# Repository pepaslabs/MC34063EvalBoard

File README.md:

# MC34063InvertingEvalBoard
An evaluation board for use with the MC34063 switcher in inverting configuration.

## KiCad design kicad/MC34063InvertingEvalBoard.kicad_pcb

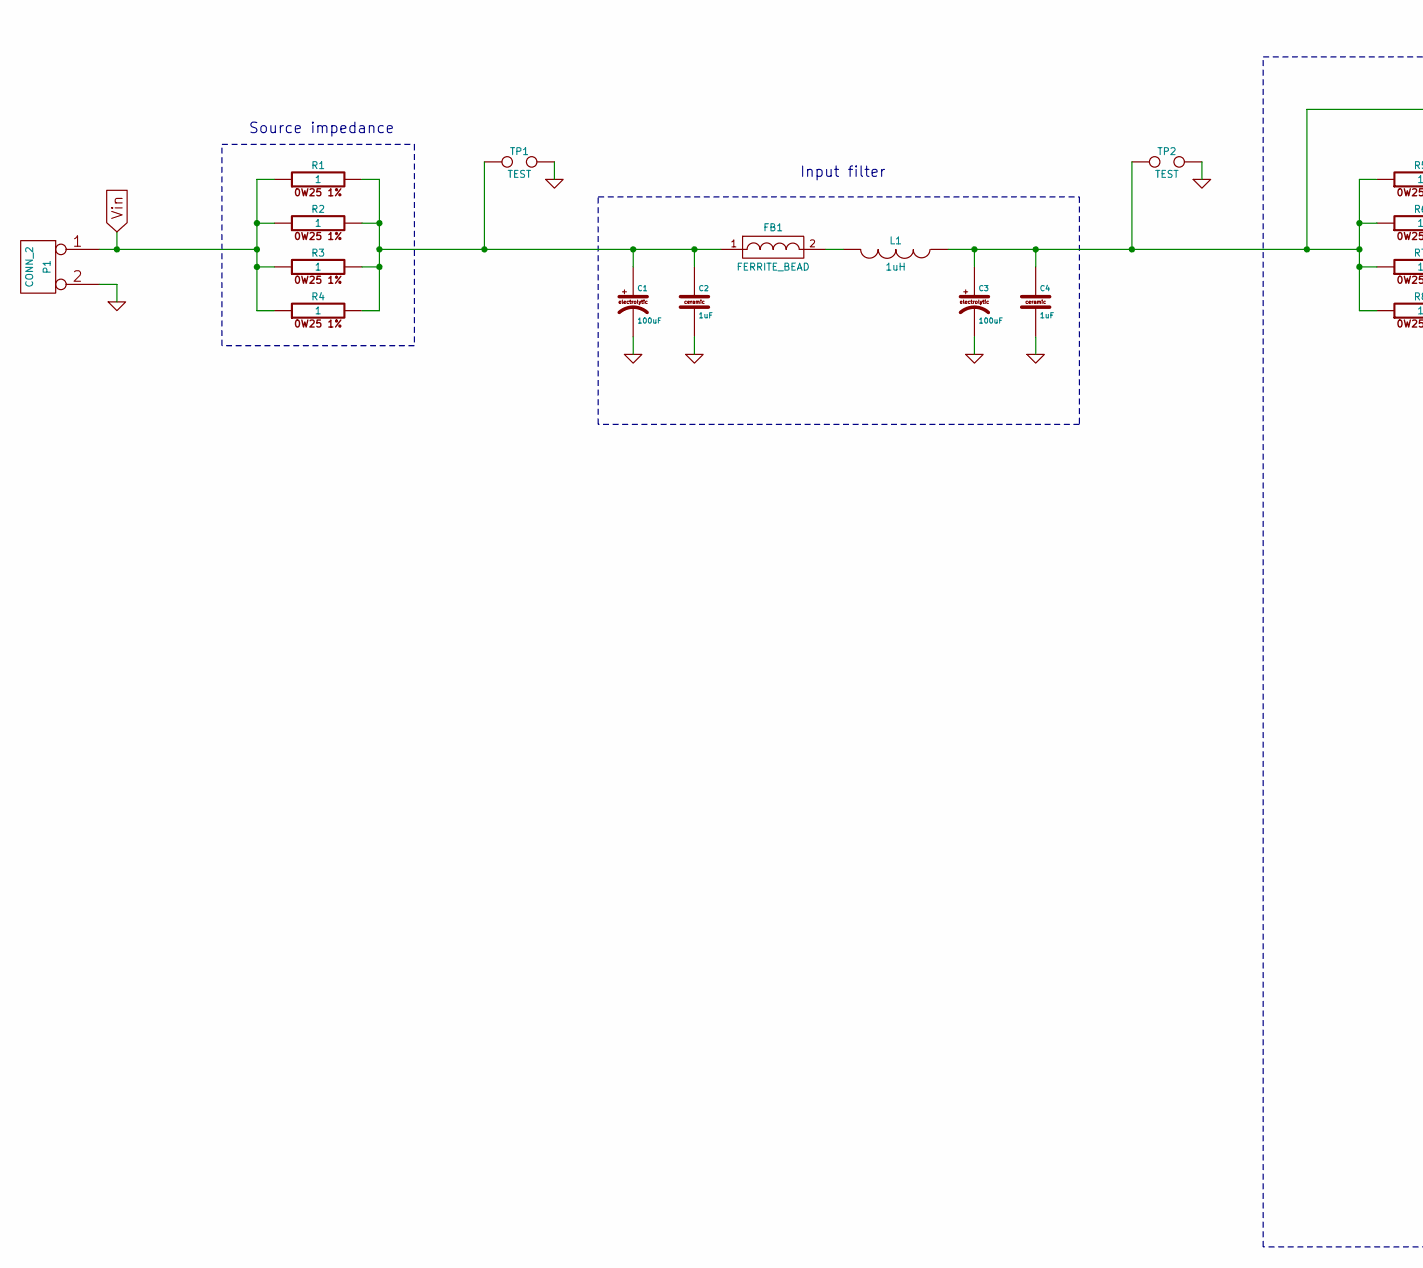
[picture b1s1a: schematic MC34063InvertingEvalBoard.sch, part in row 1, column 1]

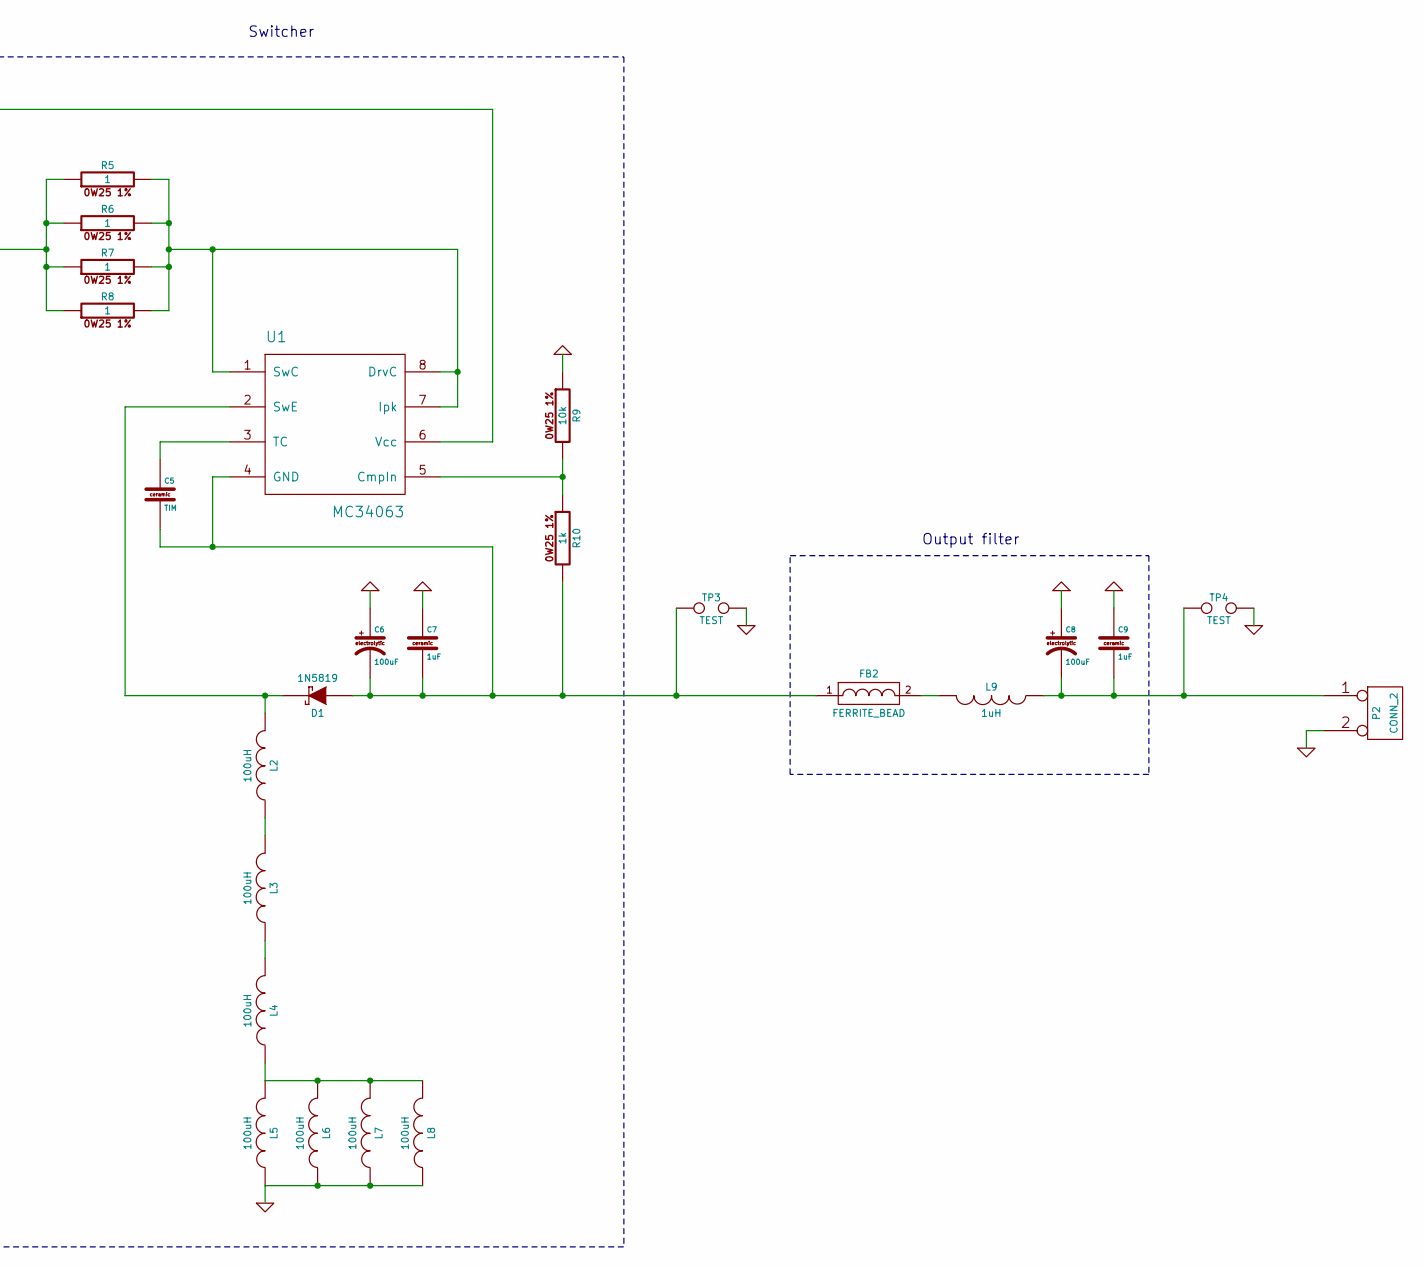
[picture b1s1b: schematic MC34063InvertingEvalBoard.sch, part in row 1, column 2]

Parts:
C1, C3, C6, C8: 100uF
C2, C4, C7, C9: 1uF
C5: TIM
D1: 1N5819
FB1, FB2: FERRITE_BEAD
L1, L9: 1uH
L2, L3, L4, L5, L6, L7, L8: 100uH
P1, P2: CONN_2
R1, R2, R3, R4, R5, R6, R7, R8: 1
R9: 10k
R10: 1k
TP1, TP2, TP3, TP4: TEST
U1: MC34063

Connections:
GND: C1.2, C2.2, C3.2, C4.2, C6.1, C7.1, C8.1, C9.1, L5.1, L6.1, L7.1, L8.1, P1.2 (PM), P2.2 (PM), R9.1, TP1.2, TP2.2, TP3.2, TP4.2
unnamed: FB1.2, L1.2
unnamed: FB2.2, L9.2
unnamed: L2.1, L3.2
unnamed: L3.1, L4.2
unnamed: L4.1, L5.2, L6.2, L7.2, L8.2
unnamed: C1.1, C2.1, FB1.1, R1.2, R2.2, R3.2, R4.2, TP1.1
unnamed: D1.2 (K), L2.2, U1.2 (SwE)
unnamed: R9.2, R10.1, U1.5 (CmpIn)
unnamed: C5.1, U1.3 (TC)
unnamed: C3.1, C4.1, L1.1, R5.1, R6.1, R7.1, R8.1, TP2.1, U1.6 (Vcc)
unnamed: R5.2, R6.2, R7.2, R8.2, U1.1 (SwC), U1.7 (Ipk), U1.8 (DrvC)
unnamed: C5.2, C6.2, C7.2, D1.1 (A), FB2.1, R10.2, TP3.1, U1.4 (GND)
unnamed: C8.2, C9.2, L9.1, P2.1, TP4.1
Vin: P1.1, R1.1, R2.1, R3.1, R4.1

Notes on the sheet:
Output filter
Input filter
Switcher
Source impedance

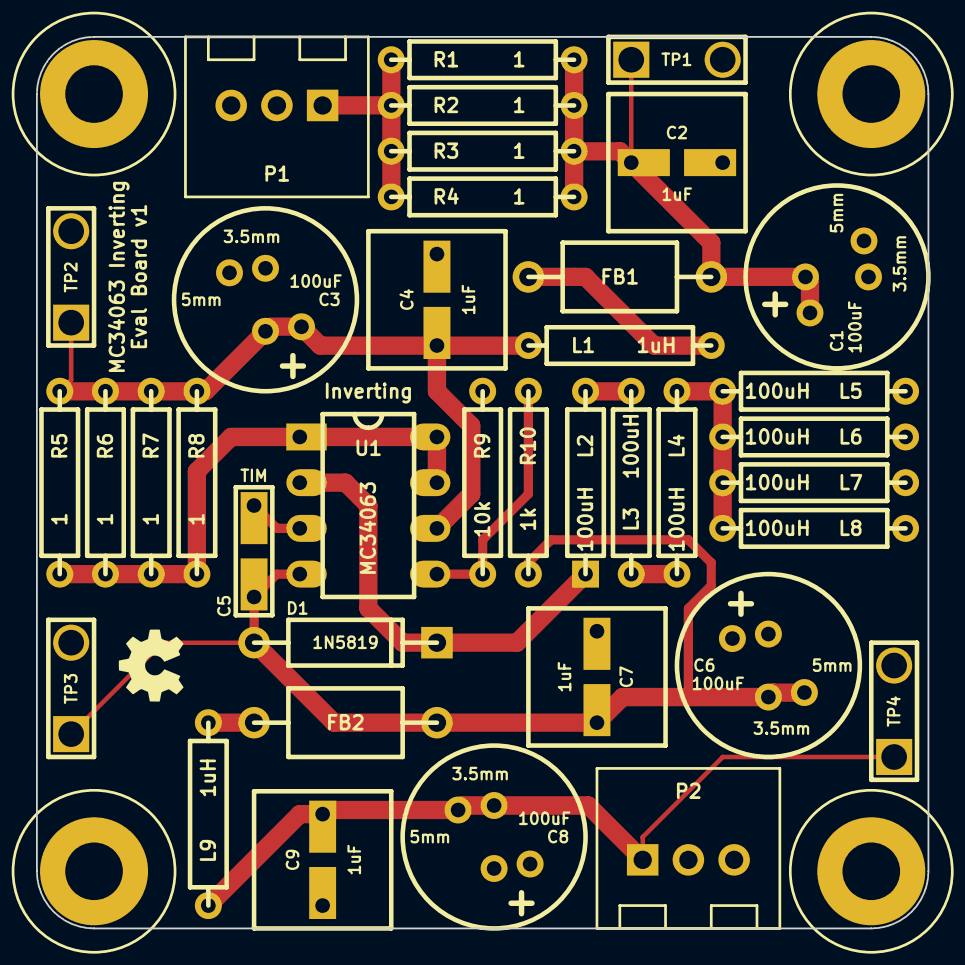
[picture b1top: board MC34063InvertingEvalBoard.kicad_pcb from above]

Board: 2 copper layers, 49.5 x 49.5 mm, 42 parts (0 on the bottom side), 15 nets.

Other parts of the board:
H***: Val**; hole_M3
H***#2, H***#3, H***#4: Val**; hole_M3

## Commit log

2015-05-10 fixing a layout bug
2015-05-10 updating board shots
